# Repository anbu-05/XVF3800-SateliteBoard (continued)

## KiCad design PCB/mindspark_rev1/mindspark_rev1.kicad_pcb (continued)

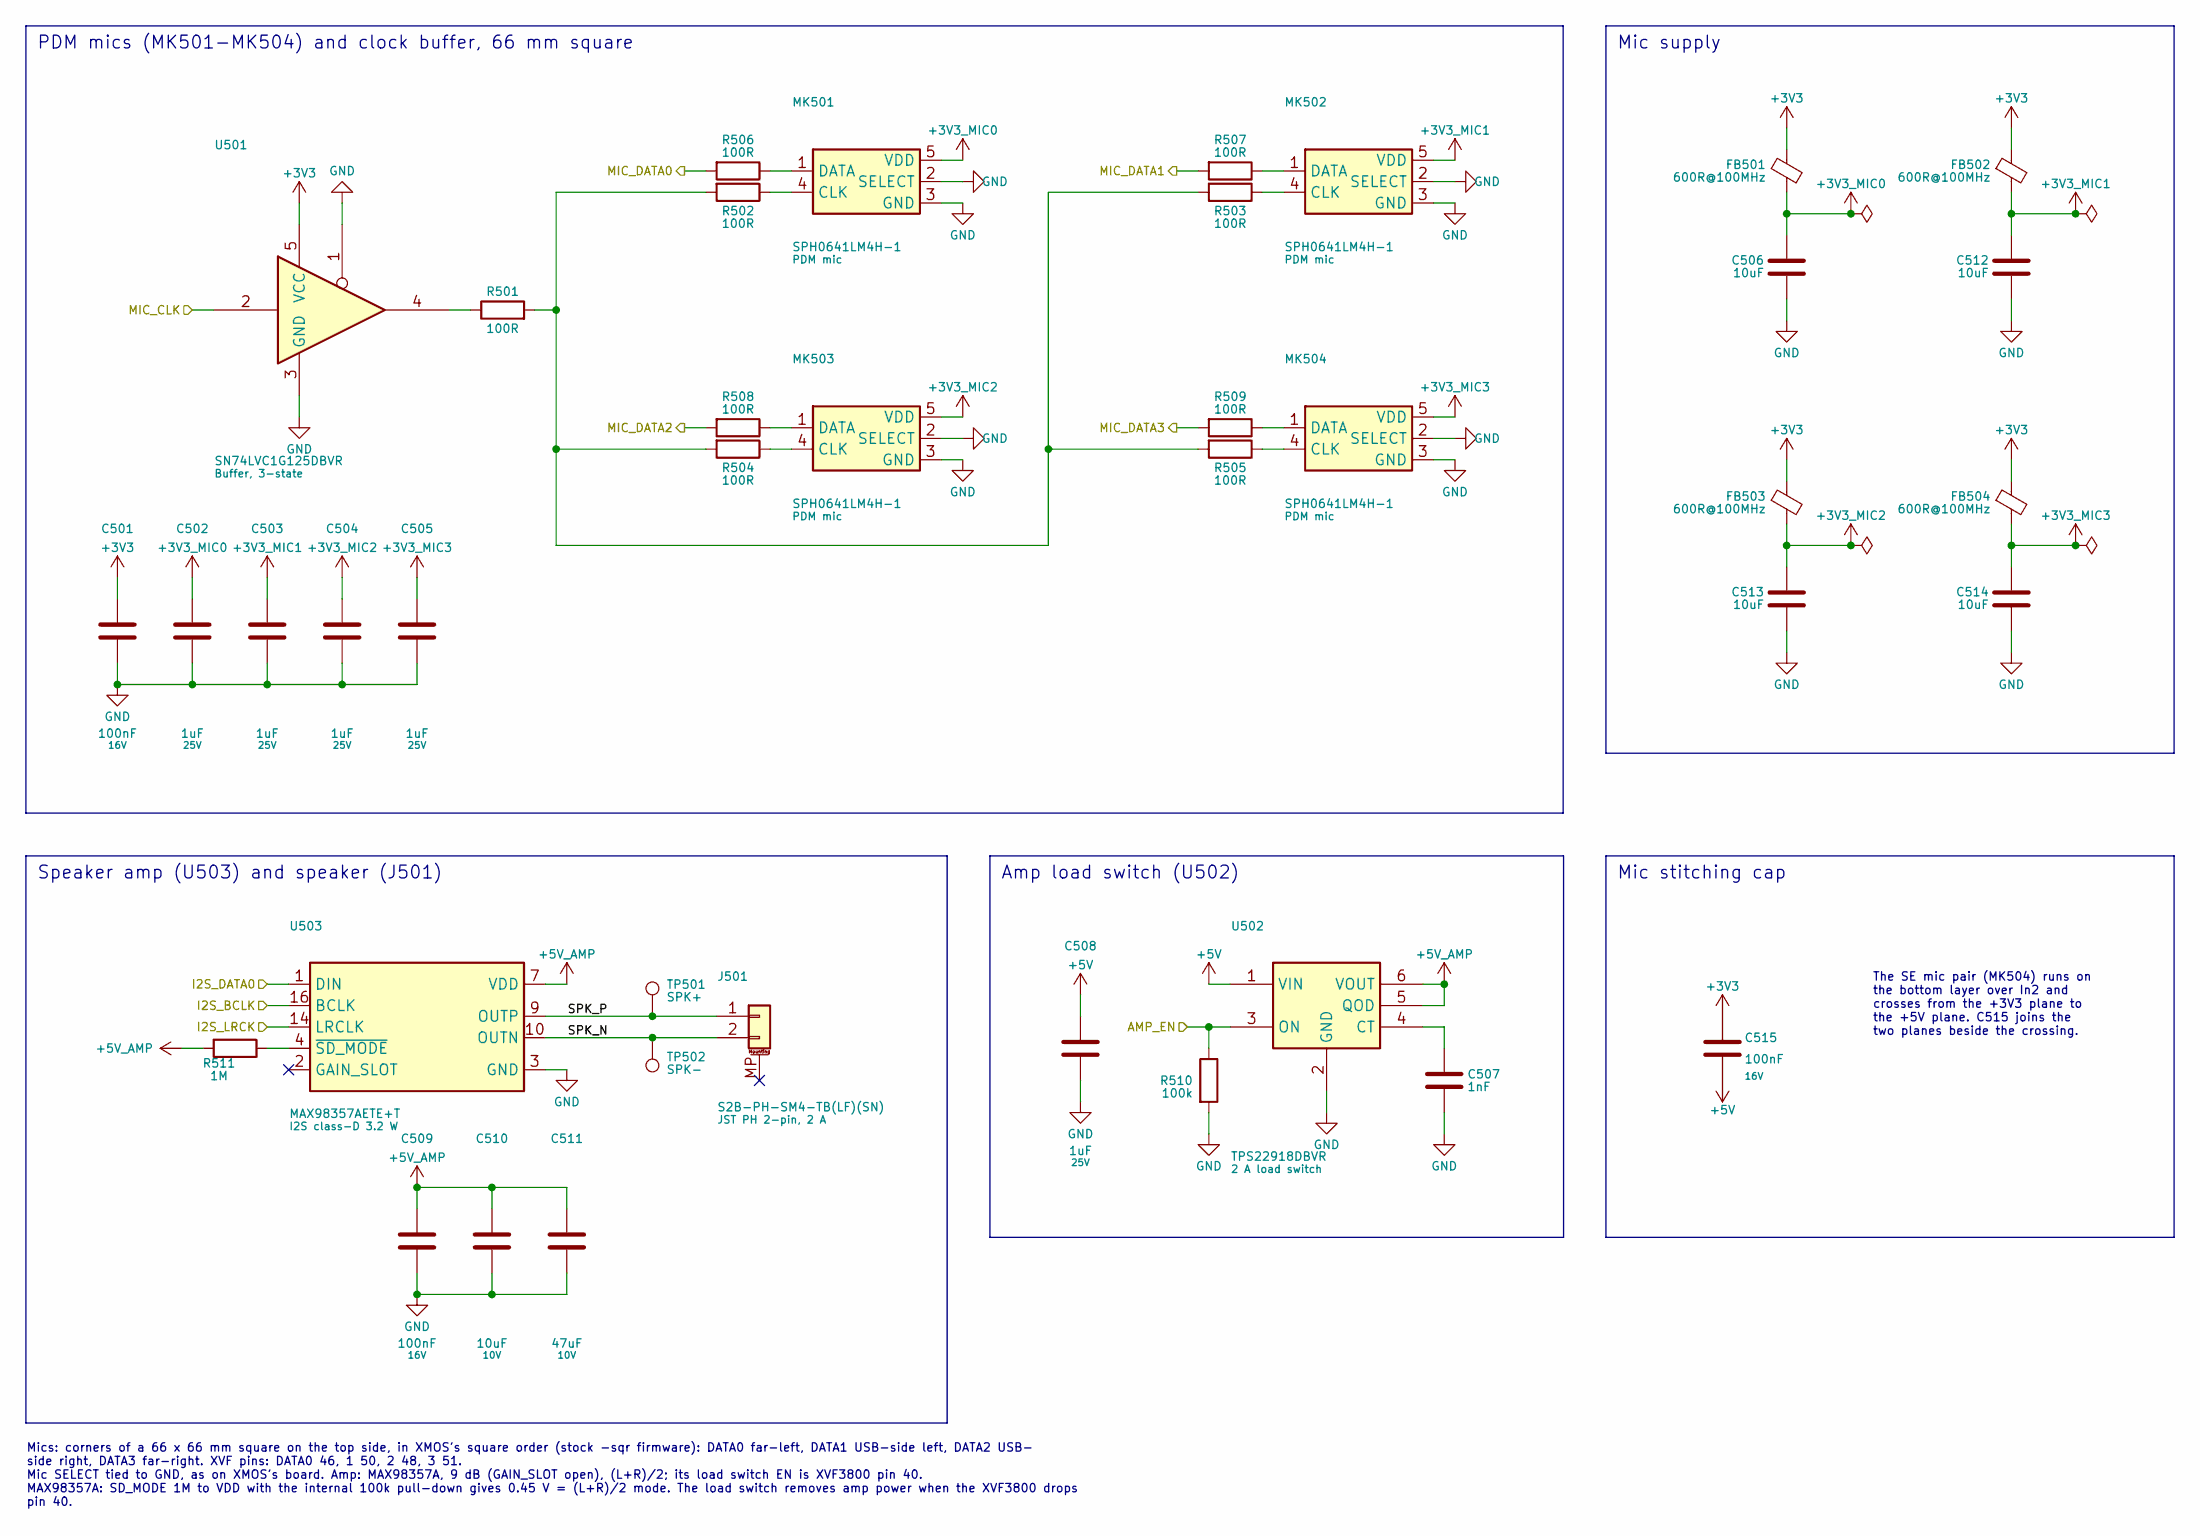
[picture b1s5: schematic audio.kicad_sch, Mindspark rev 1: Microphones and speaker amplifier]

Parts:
C501, C509, C515: 100nF; C_0402_1005Metric; voltage 16V; MPN CL05B104KO5NNNC; LCSC C1525
C502, C503, C504, C505, C508: 1uF; C_0402_1005Metric; voltage 25V; MPN CL05A105KA5NQNC; LCSC C52923
C506, C510, C512, C513, C514: 10uF; C_0603_1608Metric; voltage 10V; MPN CL10A106KP8NNNC; LCSC C19702
C507: 1nF; C_0402_1005Metric; voltage 50V; MPN 0402B102K500NT; LCSC C1523
C511: 47uF; C_1206_3216Metric; voltage 10V; MPN CL31A476MPHNNNE; LCSC C96123
FB501, FB502, FB503, FB504: 600R@100MHz; L_0402_1005Metric; MPN BLM15AG601SN1D; LCSC C76884
J501: S2B-PH-SM4-TB(LF)(SN); JST_PH_S2B-PH-SM4-TB_1x02-1MP_P2.00mm_Horizontal; MPN S2B-PH-SM4-TB(LF)(SN); LCSC C295747
MK501, MK502, MK503, MK504: SPH0641LM4H-1; Knowles_SPH0641LM4H-1_LGA-5_3.5x2.65mm; MPN SPH0641LM4H-1; LCSC C497724
R501, R502, R503, R504, R505, R506, R507, R508, R509: 100R; R_0402_1005Metric; tolerance 1%; MPN 0402WGF1000TCE; LCSC C25076
R510: 100k; R_0402_1005Metric; tolerance 1%; MPN 0402WGF1003TCE; LCSC C25741
R511: 1M; R_0402_1005Metric; tolerance 1%; MPN 0402WGF1004TCE; LCSC C26083
TP501: SPK+; TestPoint_Pad_1.0x1.0mm
TP502: SPK-; TestPoint_Pad_1.0x1.0mm
U501: SN74LVC1G125DBVR; SOT-23-5; MPN SN74LVC1G125DBVR; LCSC C23654
U502: TPS22918DBVR; SOT-23-6; MPN TPS22918DBVR; LCSC C131941
U503: MAX98357AETE+T; TQFN-16-1EP_3x3mm_P0.5mm_EP1.23x1.23mm; MPN MAX98357AETE+T; LCSC C910544

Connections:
+3V3: C501.1, C515.1, FB501.1, FB502.1, FB503.1, FB504.1, U501.5 (VCC); also elsewhere on the board
+3V3_MIC0: C502.1, C506.1, FB501.2, MK501.5 (VDD)
+3V3_MIC1: C503.1, C512.1, FB502.2, MK502.5 (VDD)
+3V3_MIC2: C504.1, C513.1, FB503.2, MK503.5 (VDD)
+3V3_MIC3: C505.1, C514.1, FB504.2, MK504.5 (VDD)
+5V: C508.1, C515.2, U502.1 (VIN); also elsewhere on the board
+5V_AMP: C509.1, C510.1, C511.1, R511.2, U502.5 (QOD), U502.6 (VOUT), U503.7 (VDD), U503.8 (VDD)
/AMP_EN: R510.1, U502.3 (ON); also elsewhere on the board
/I2S_BCLK: U503.16 (BCLK); also elsewhere on the board
/I2S_DATA0: U503.1 (DIN); also elsewhere on the board
/I2S_LRCK: U503.14 (LRCLK); also elsewhere on the board
/MIC_CLK: U501.2; also elsewhere on the board
/MIC_DATA0: R506.2; also elsewhere on the board
/MIC_DATA1: R507.2; also elsewhere on the board
/MIC_DATA2: R508.2; also elsewhere on the board
/MIC_DATA3: R509.2; also elsewhere on the board
/audio/SPK_N: J501.2, TP502.1 (1_1), U503.10 (OUTN)
/audio/SPK_P: J501.1, TP501.1 (1_1), U503.9 (OUTP)
GND: C501.2, C502.2, C503.2, C504.2, C505.2, C506.2, C507.2, C508.2, C509.2, C510.2, C511.2, C512.2, C513.2, C514.2, MK501.2 (SELECT), MK501.3 (GND), MK502.2 (SELECT), MK502.3 (GND), MK503.2 (SELECT), MK503.3 (GND), MK504.2 (SELECT), MK504.3 (GND), R510.2, U501.1, U501.3 (GND), U502.2 (GND), U503.3 (GND), U503.11 (GND), U503.15 (GND), U503.17 (GND); also elsewhere on the board
unnamed: MK501.4 (CLK), R502.1
unnamed: MK501.1 (DATA), R506.1
unnamed: MK502.4 (CLK), R503.1
unnamed: MK502.1 (DATA), R507.1
unnamed: MK503.4 (CLK), R504.1
unnamed: MK503.1 (DATA), R508.1
unnamed: MK504.4 (CLK), R505.1
unnamed: MK504.1 (DATA), R509.1
unnamed: R501.1, U501.4
unnamed: R501.2, R502.2, R503.2, R504.2, R505.2
unnamed: C507.1, U502.4 (CT)
unnamed: R511.1, U503.4 (~SD_MODE)

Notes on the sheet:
Mics: corners of a 66 x 66 mm square on the top side, in XMOS's square order (stock -sqr firmware): DATA0 far-left, DATA1 USB-side left, DATA2 USB- side right, DATA3 far-right. XVF pins: DATA0 46, 1 50, 2 48, 3 51. Mic SELECT tied to GND, as on XMOS's board. Amp: MAX98357A, 9 dB (GAIN_SLOT open), (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
PDM mics (MK501-MK504) and clock buffer, 66 mm square
Mic supply
Speaker amp (U503) and speaker (J501)
Amp load switch (U502)
Mic stitching cap
The SE mic pair (MK504) runs on the bottom layer over In2 and crosses from the +3V3 plane to the +5V plane. C515 joins the two planes beside the crossing.

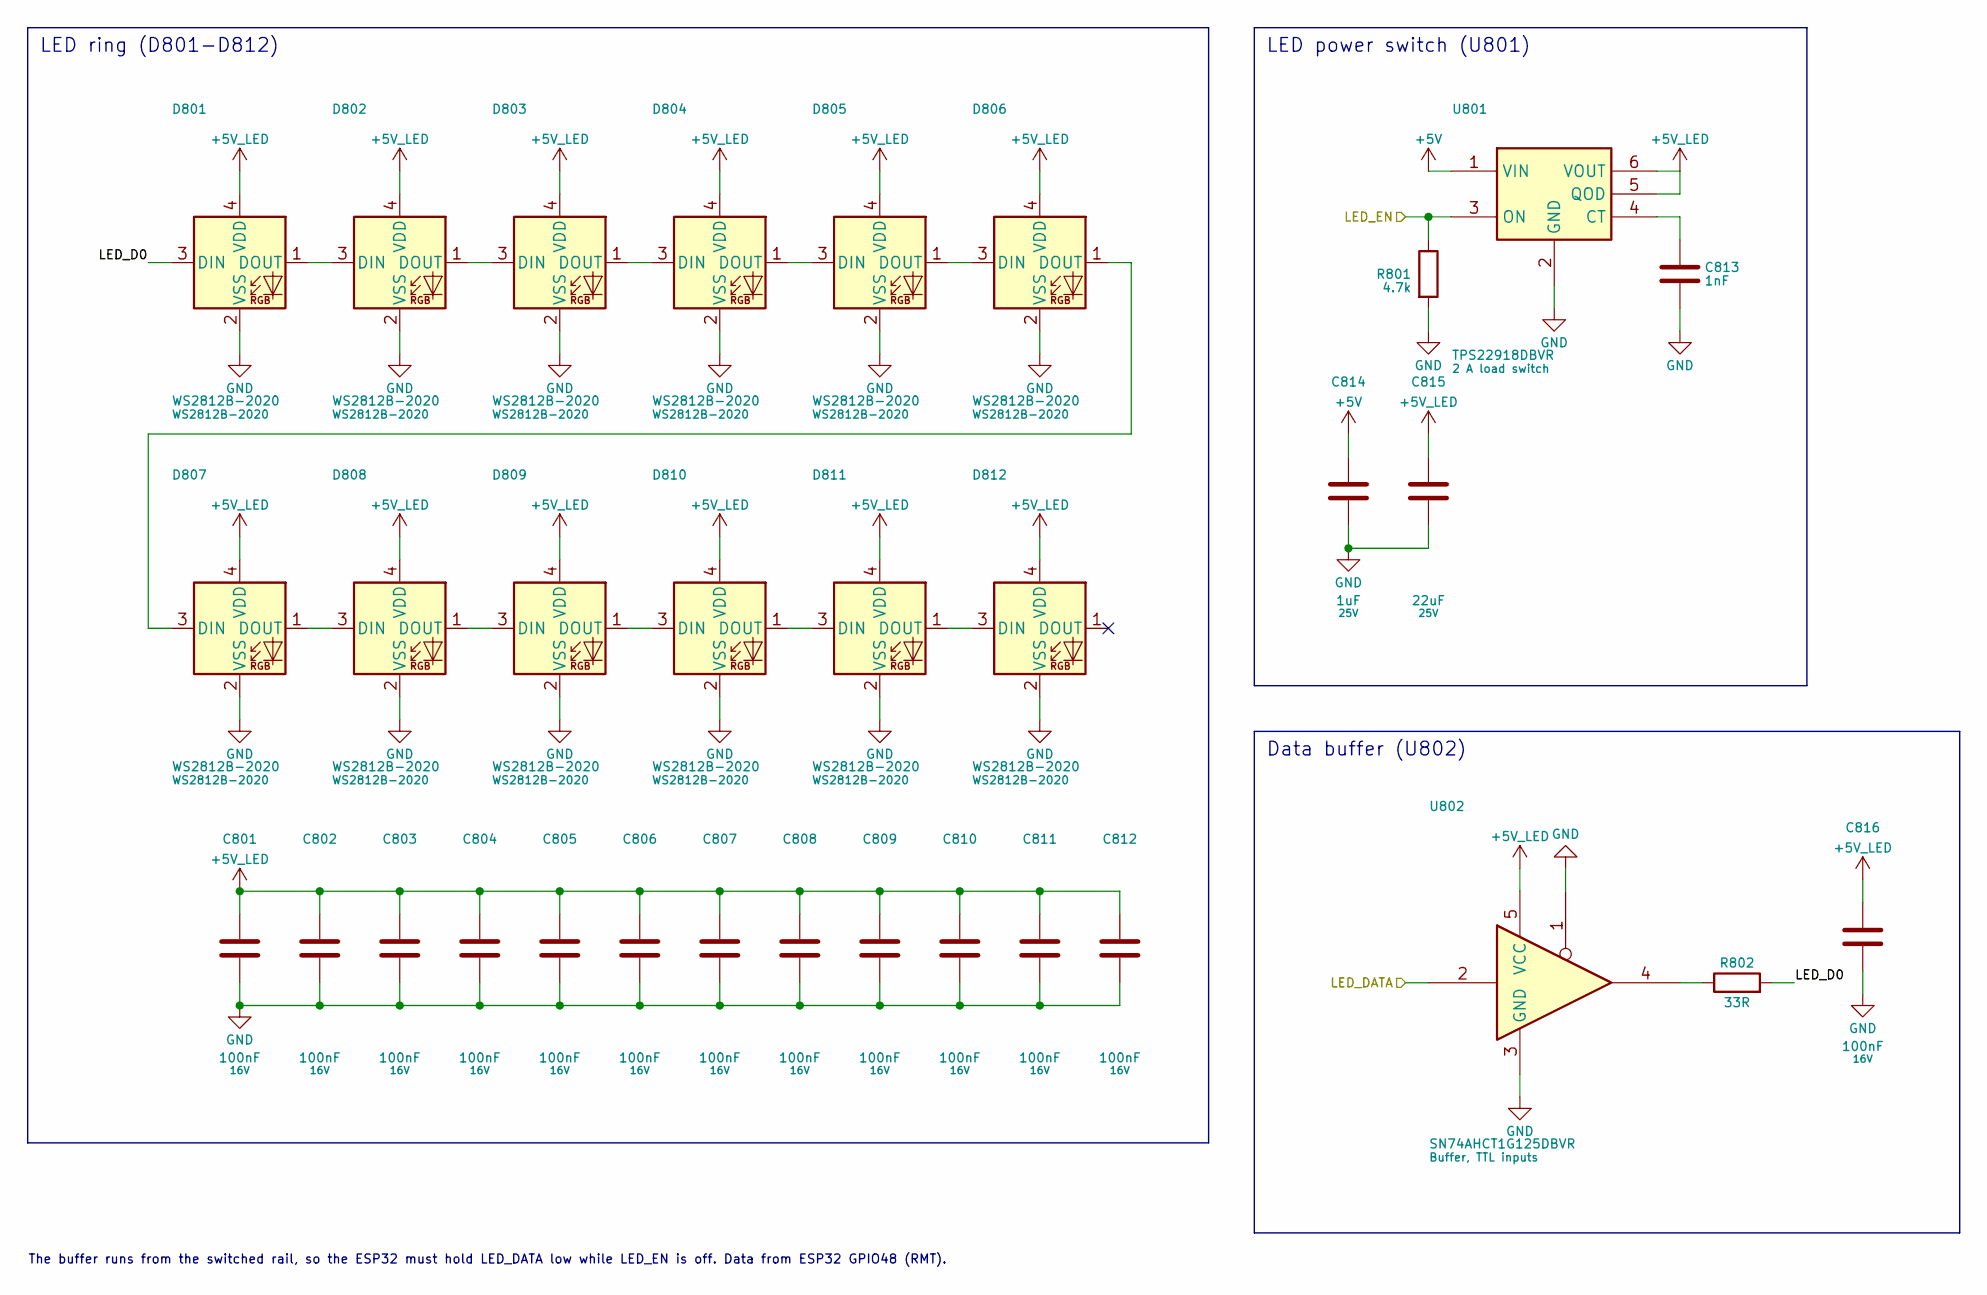
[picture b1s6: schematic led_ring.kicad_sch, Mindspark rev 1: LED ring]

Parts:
C801, C802, C803, C804, C805, C806, C807, C808, C809, C810, C811, C812, C816: 100nF; C_0402_1005Metric; voltage 16V; MPN CL05B104KO5NNNC; LCSC C1525
C813: 1nF; C_0402_1005Metric; voltage 50V; MPN 0402B102K500NT; LCSC C1523
C814: 1uF; C_0402_1005Metric; voltage 25V; MPN CL05A105KA5NQNC; LCSC C52923
C815: 22uF; C_0805_2012Metric; voltage 25V; MPN CL21A226MAQNNNE; LCSC C45783
D801, D802, D803, D804, D805, D806, D807, D808, D809, D810, D811, D812: WS2812B-2020; LED_WS2812B-2020_PLCC4_2.0x2.0mm; MPN WS2812B-2020-V6; LCSC C52917434
R801: 4.7k; R_0402_1005Metric; tolerance 1%; MPN 0402WGF4701TCE; LCSC C25900
R802: 33R; R_0402_1005Metric; tolerance 1%; MPN 0402WGF330JTCE; LCSC C25105
U801: TPS22918DBVR; SOT-23-6; MPN TPS22918DBVR; LCSC C131941
U802: SN74AHCT1G125DBVR; SOT-23-5; MPN SN74AHCT1G125DBVR; LCSC C7484

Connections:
+5V: C814.1, U801.1 (VIN); also elsewhere on the board
+5V_LED: C801.1, C802.1, C803.1, C804.1, C805.1, C806.1, C807.1, C808.1, C809.1, C810.1, C811.1, C812.1, C815.1, C816.1, D801.4 (VDD), D802.4 (VDD), D803.4 (VDD), D804.4 (VDD), D805.4 (VDD), D806.4 (VDD), D807.4 (VDD), D808.4 (VDD), D809.4 (VDD), D810.4 (VDD), D811.4 (VDD), D812.4 (VDD), U801.5 (QOD), U801.6 (VOUT), U802.5 (VCC)
/LED_DATA: U802.2; also elsewhere on the board
/LED_EN: R801.1, U801.3 (ON); also elsewhere on the board
/led_ring/LED_D0: D801.3 (DIN), R802.2
GND: C801.2, C802.2, C803.2, C804.2, C805.2, C806.2, C807.2, C808.2, C809.2, C810.2, C811.2, C812.2, C813.2, C814.2, C815.2, C816.2, D801.2 (VSS), D802.2 (VSS), D803.2 (VSS), D804.2 (VSS), D805.2 (VSS), D806.2 (VSS), D807.2 (VSS), D808.2 (VSS), D809.2 (VSS), D810.2 (VSS), D811.2 (VSS), D812.2 (VSS), R801.2, U801.2 (GND), U802.1, U802.3 (GND); also elsewhere on the board
unnamed: D801.1 (DOUT), D802.3 (DIN)
unnamed: D802.1 (DOUT), D803.3 (DIN)
unnamed: D803.1 (DOUT), D804.3 (DIN)
unnamed: D804.1 (DOUT), D805.3 (DIN)
unnamed: D805.1 (DOUT), D806.3 (DIN)
unnamed: D806.1 (DOUT), D807.3 (DIN)
unnamed: D807.1 (DOUT), D808.3 (DIN)
unnamed: D808.1 (DOUT), D809.3 (DIN)
unnamed: D809.1 (DOUT), D810.3 (DIN)
unnamed: D810.1 (DOUT), D811.3 (DIN)
unnamed: D811.1 (DOUT), D812.3 (DIN)
unnamed: R802.1, U802.4
unnamed: C813.1, U801.4 (CT)

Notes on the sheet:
The buffer runs from the switched rail, so the ESP32 must hold LED_DATA low while LED_EN is off. Data from ESP32 GPIO48 (RMT).
LED power switch (U801)
Data buffer (U802)
LED ring (D801-D812)

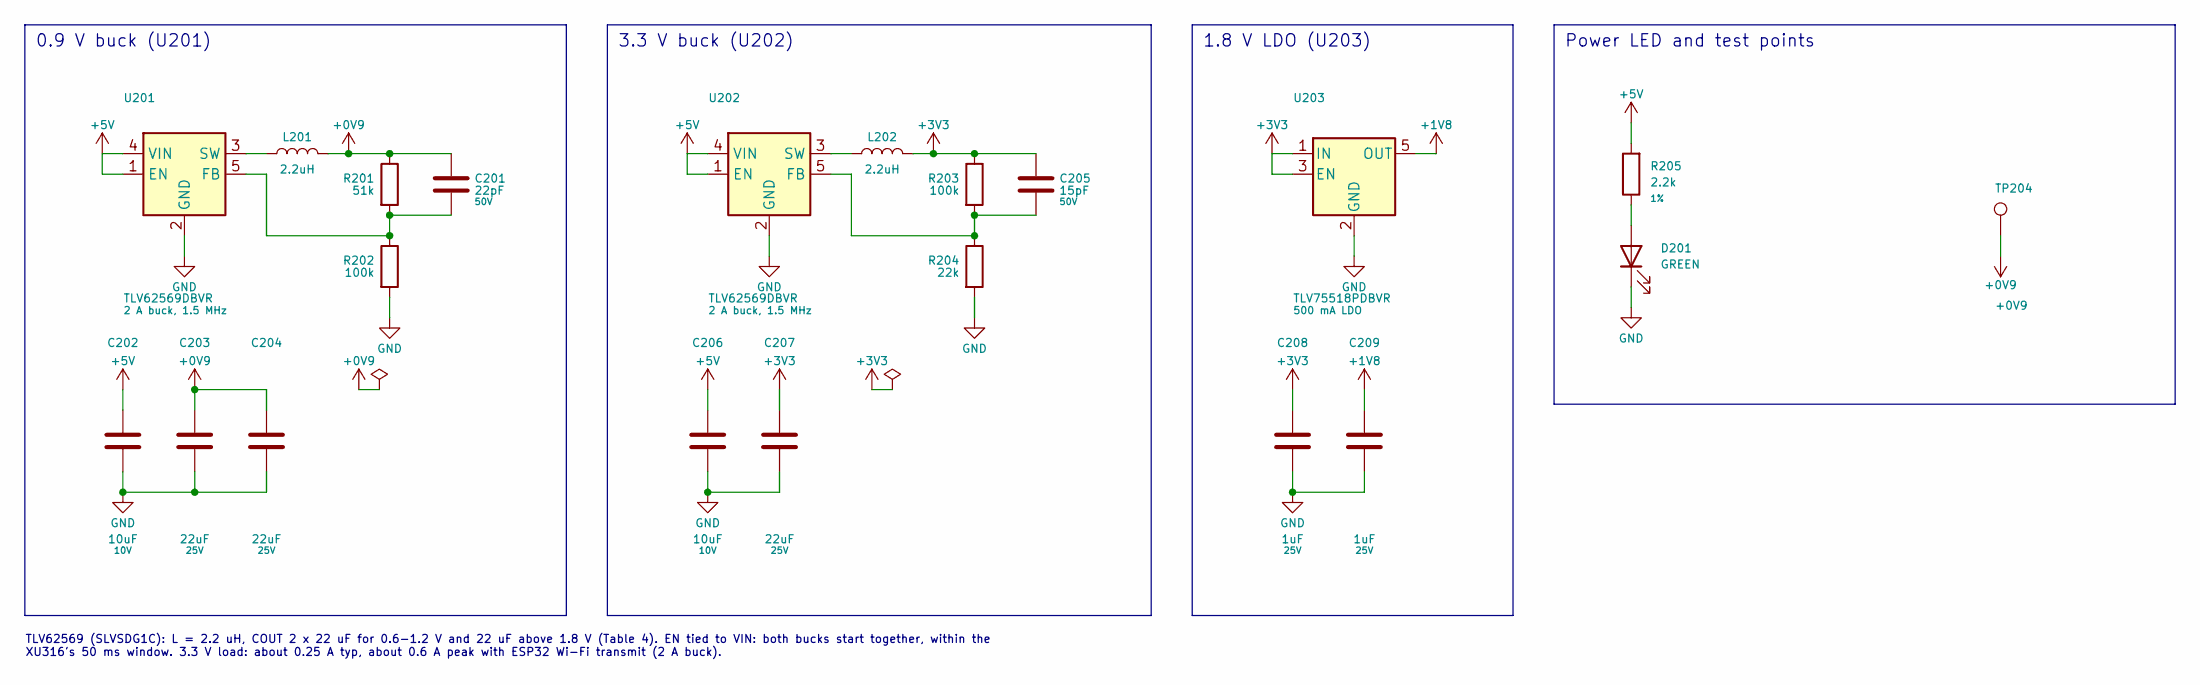
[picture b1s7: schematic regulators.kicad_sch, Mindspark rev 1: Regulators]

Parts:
C201: 22pF; C_0402_1005Metric; voltage 50V; MPN 0402CG220J500NT; LCSC C1555
C202, C206: 10uF; C_0603_1608Metric; voltage 10V; MPN CL10A106KP8NNNC; LCSC C19702
C203, C204, C207: 22uF; C_0805_2012Metric; voltage 25V; MPN CL21A226MAQNNNE; LCSC C45783
C205: 15pF; C_0402_1005Metric; voltage 50V; MPN 0402CG150J500NT; LCSC C1548
C208, C209: 1uF; C_0402_1005Metric; voltage 25V; MPN CL05A105KA5NQNC; LCSC C52923
D201: GREEN; LED_0603_1608Metric; MPN KT-0603G; LCSC C12624
L201, L202: 2.2uH; L_Bourns_SRP4020TA; MPN SRP4020TA-2R2M; LCSC C719179
R201: 51k; R_0402_1005Metric; tolerance 1%; MPN 0402WGF5102TCE; LCSC C25794
R202, R203: 100k; R_0402_1005Metric; tolerance 1%; MPN 0402WGF1003TCE; LCSC C25741
R204: 22k; R_0402_1005Metric; tolerance 1%; MPN 0402WGF2202TCE; LCSC C25768
R205: 2.2k; R_0402_1005Metric; tolerance 1%; MPN 0402WGF2201TCE; LCSC C25879
TP204: +0V9; TestPoint_Pad_D1.0mm
U201, U202: TLV62569DBVR; SOT-23-5; MPN TLV62569DBVR; LCSC C141836
U203: TLV75518PDBVR; SOT-23-5; MPN TLV75518PDBVR; LCSC C2877863

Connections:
+0V9: C201.1, C203.1, C204.1, L201.2, R201.1, TP204.1 (1_1); also elsewhere on the board
+1V8: C209.1, U203.5 (OUT); also elsewhere on the board
+3V3: C205.1, C207.1, C208.1, L202.2, R203.1, U203.1 (IN), U203.3 (EN); also elsewhere on the board
+5V: C202.1, C206.1, R205.2, U201.1 (EN), U201.4 (VIN), U202.1 (EN), U202.4 (VIN); also elsewhere on the board
GND: C202.2, C203.2, C204.2, C206.2, C207.2, C208.2, C209.2, D201.1 (K), R202.2, R204.2, U201.2 (GND), U202.2 (GND), U203.2 (GND); also elsewhere on the board
unnamed: D201.2 (A), R205.1
unnamed: C201.2, R201.2, R202.1, U201.5 (FB)
unnamed: L201.1, U201.3 (SW)
unnamed: C205.2, R203.2, R204.1, U202.5 (FB)
unnamed: L202.1, U202.3 (SW)

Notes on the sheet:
0.9 V buck (U201)
Power LED and test points
1.8 V LDO (U203)
3.3 V buck (U202)
TLV62569 (SLVSDG1C): L = 2.2 uH, COUT 2 x 22 uF for 0.6-1.2 V and 22 uF above 1.8 V (Table 4). EN tied to VIN: both bucks start together, within the XU316's 50 ms window. 3.3 V load: about 0.25 A typ, about 0.6 A peak with ESP32 Wi-Fi transmit (2 A buck).

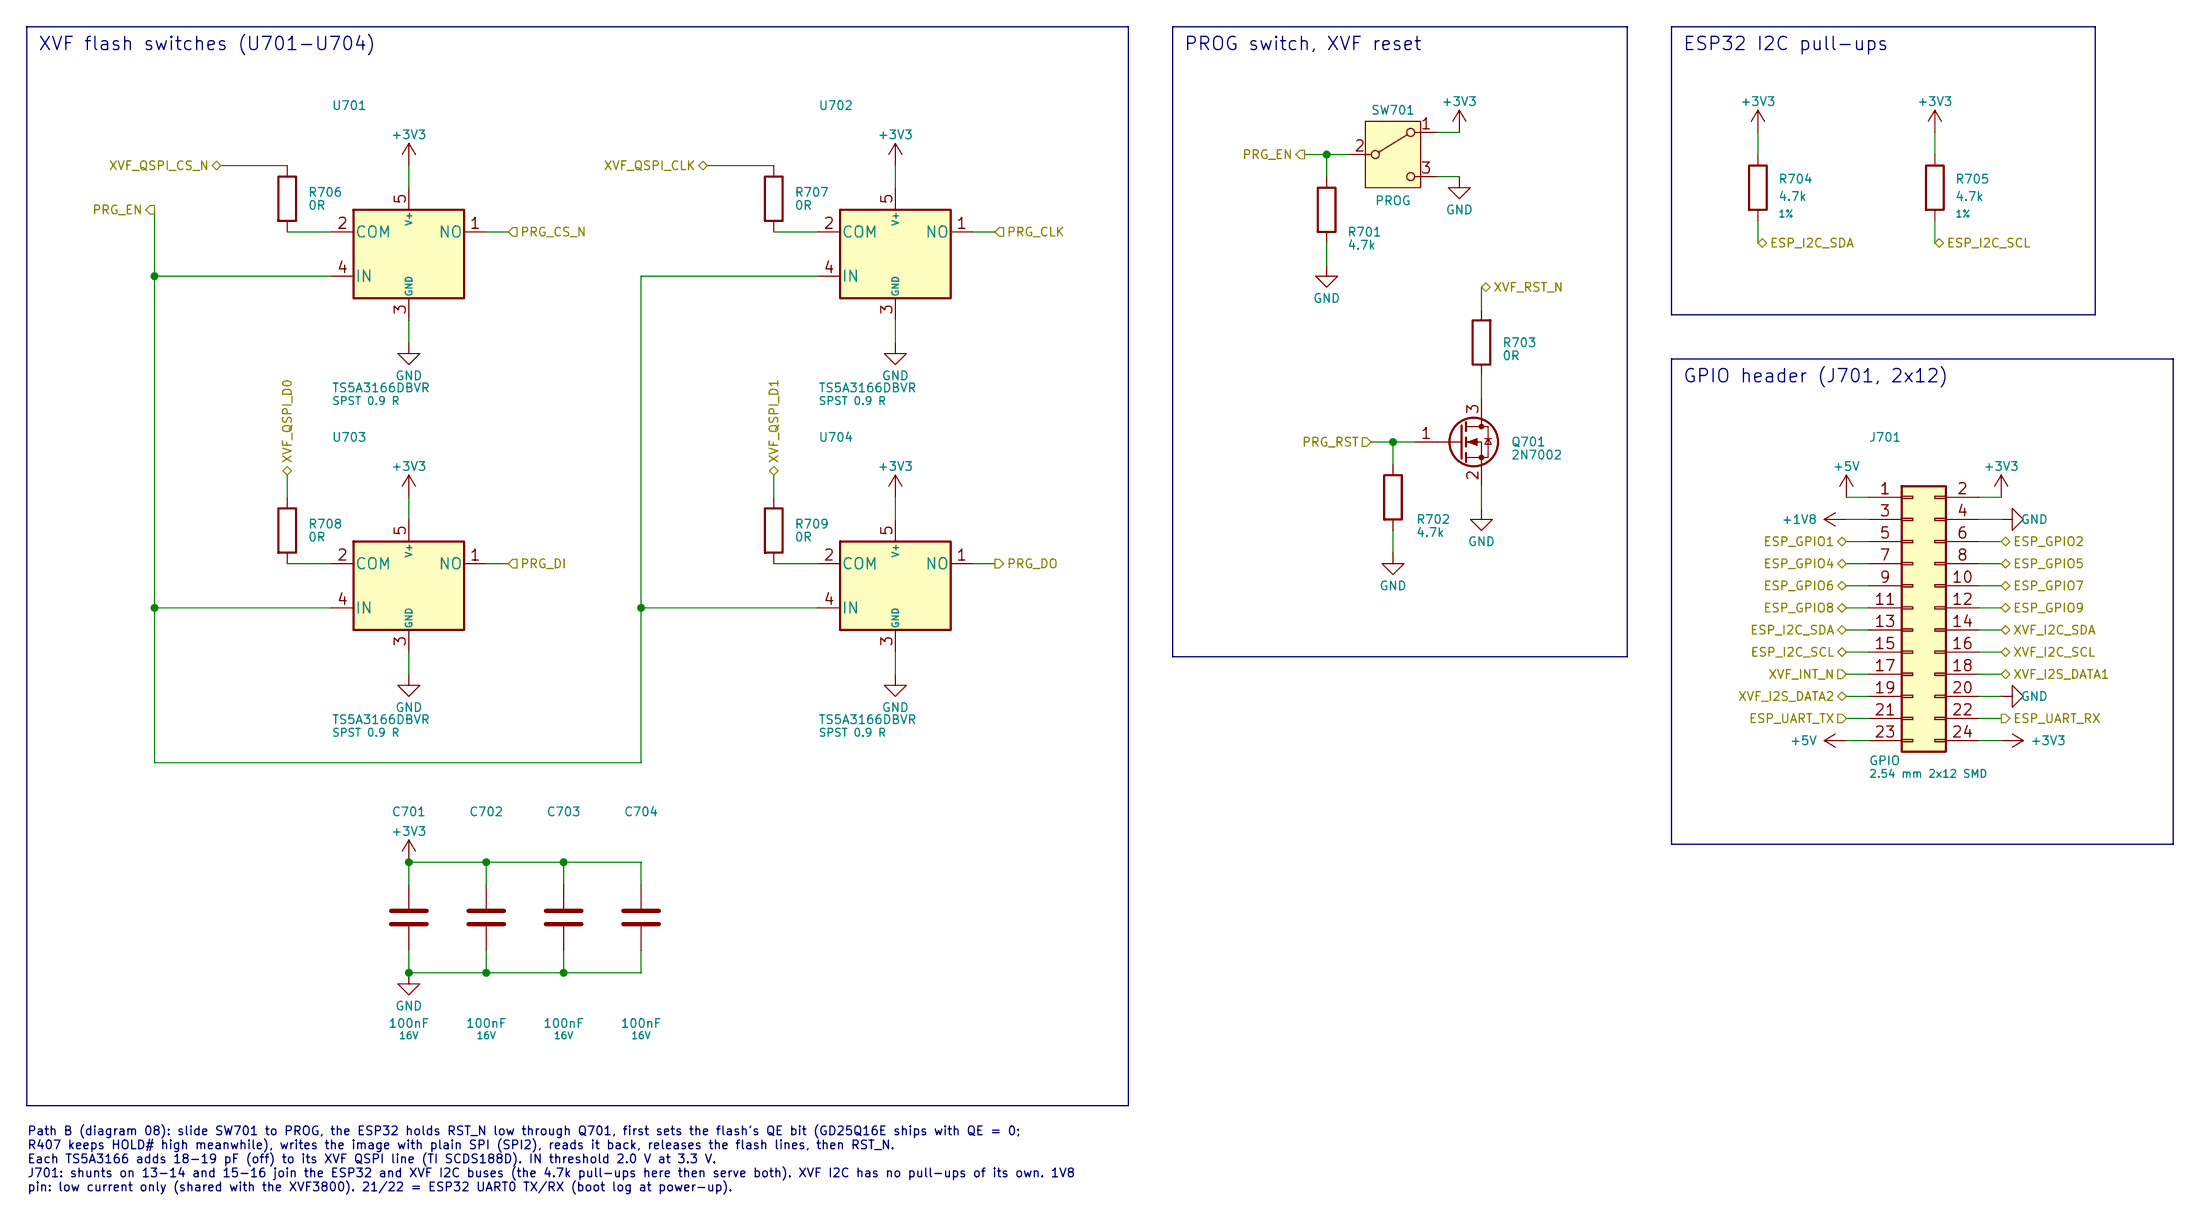
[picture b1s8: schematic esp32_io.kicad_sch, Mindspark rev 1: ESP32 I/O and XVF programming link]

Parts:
C701, C702, C703, C704: 100nF; C_0402_1005Metric; voltage 16V; MPN CL05B104KO5NNNC; LCSC C1525
J701: GPIO; PinHeader_2x12_P2.54mm_Vertical_SMD_HCTL_PZ254; MPN PZ254-2-12-S; LCSC C3294470
Q701: 2N7002; SOT-23; MPN 2N7002; LCSC C8545
R701, R702, R704, R705: 4.7k; R_0402_1005Metric; tolerance 1%; MPN 0402WGF4701TCE; LCSC C25900
R703, R706, R707, R708, R709: 0R; R_0402_1005Metric; tolerance 1%; MPN 0402WGF0000TCE; LCSC C17168
SW701: PROG; SW_SHOUHAN_MSK12C02_SideActuated; MPN MSK12C02; LCSC C431540
U701, U702, U703, U704: TS5A3166DBVR; SOT-23-5; MPN TS5A3166DBVR; LCSC C353035

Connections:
+1V8: J701.3; also elsewhere on the board
+3V3: C701.1, C702.1, C703.1, C704.1, J701.2, J701.24, R704.1, R705.1, SW701.1 (A), U701.5 (V+), U702.5 (V+), U703.5 (V+), U704.5 (V+); also elsewhere on the board
+5V: J701.1, J701.23; also elsewhere on the board
/ESP_GPIO1: J701.5; also elsewhere on the board
/ESP_GPIO2: J701.6; also elsewhere on the board
/ESP_GPIO4: J701.7; also elsewhere on the board
/ESP_GPIO5: J701.8; also elsewhere on the board
/ESP_GPIO6: J701.9; also elsewhere on the board
/ESP_GPIO7: J701.10; also elsewhere on the board
/ESP_GPIO8: J701.11; also elsewhere on the board
/ESP_GPIO9: J701.12; also elsewhere on the board
/ESP_I2C_SCL: J701.15, R705.2; also elsewhere on the board
/ESP_I2C_SDA: J701.13, R704.2; also elsewhere on the board
/ESP_UART_RX: J701.22; also elsewhere on the board
/ESP_UART_TX: J701.21; also elsewhere on the board
/PRG_CLK: U702.1 (NO); also elsewhere on the board
/PRG_CS_N: U701.1 (NO); also elsewhere on the board
/PRG_DI: U703.1 (NO); also elsewhere on the board
/PRG_DO: U704.1 (NO); also elsewhere on the board
/PRG_EN: R701.1, SW701.2 (B), U701.4 (IN), U702.4 (IN), U703.4 (IN), U704.4 (IN); also elsewhere on the board
/PRG_RST: Q701.1 (G), R702.1; also elsewhere on the board
/XVF_I2C_SCL: J701.16; also elsewhere on the board
/XVF_I2C_SDA: J701.14; also elsewhere on the board
/XVF_I2S_DATA1: J701.18; also elsewhere on the board
/XVF_I2S_DATA2: J701.19; also elsewhere on the board
/XVF_INT_N: J701.17; also elsewhere on the board
/XVF_QSPI_CLK: R707.1; also elsewhere on the board
/XVF_QSPI_CS_N: R706.1; also elsewhere on the board
/XVF_QSPI_D0: R708.1; also elsewhere on the board
/XVF_QSPI_D1: R709.1; also elsewhere on the board
/XVF_RST_N: R703.2; also elsewhere on the board
GND: C701.2, C702.2, C703.2, C704.2, J701.4, J701.20, Q701.2 (S), R701.2, R702.2, SW701.3 (C), U701.3 (GND), U702.3 (GND), U703.3 (GND), U704.3 (GND); also elsewhere on the board
unnamed: Q701.3 (D), R703.1
unnamed: R706.2, U701.2 (COM)
unnamed: R707.2, U702.2 (COM)
unnamed: R708.2, U703.2 (COM)
unnamed: R709.2, U704.2 (COM)

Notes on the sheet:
XVF flash switches (U701-U704)
ESP32 I2C pull-ups
PROG switch, XVF reset
GPIO header (J701, 2x12)
Path B (diagram 08): slide SW701 to PROG, the ESP32 holds RST_N low through Q701, first sets the flash's QE bit (GD25Q16E ships with QE = 0; R407 keeps HOLD# high meanwhile), writes the image with plain SPI (SPI2), reads it back, releases the flash lines, then RST_N. Each TS5A3166 adds 18-19 pF (of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

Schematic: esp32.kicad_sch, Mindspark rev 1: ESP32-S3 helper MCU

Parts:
C601: 22uF; C_0805_2012Metric; voltage 25V; MPN CL21A226MAQNNNE; LCSC C45783
C602, C604, C605: 100nF; C_0402_1005Metric; voltage 16V; MPN CL05B104KO5NNNC; LCSC C1525
C603: 1uF; C_0402_1005Metric; voltage 25V; MPN CL05A105KA5NQNC; LCSC C52923
D601: WS2812B-2020; LED_WS2812B-2020_PLCC4_2.0x2.0mm; MPN WS2812B-2020-V6; LCSC C52917434
R601, R602, R607: 10k; R_0402_1005Metric; tolerance 1%; MPN 0402WGF1002TCE; LCSC C25744
R603, R604, R609: 1k; R_0402_1005Metric; tolerance 1%; MPN 0402WGF1001TCE; LCSC C11702
R605, R606: 27R; R_0402_1005Metric; tolerance 1%; MPN 0402WGF270JTCE; LCSC C25100
R608: 33R; R_0402_1005Metric; tolerance 1%; MPN 0402WGF330JTCE; LCSC C25105
SW601: EN; SW_Push_1P1T_XKB_TS-1187A; MPN TS-1187A-B-A-B; LCSC C318884
SW602: BOOT; SW_Push_1P1T_XKB_TS-1187A; MPN TS-1187A-B-A-B; LCSC C318884
SW603: USER; SW_SHOUHAN_TS24CA_SideActuated; MPN TS24CA; LCSC C393942
U601: ESP32-S3-WROOM-1U-N16R8; ESP32-S3-WROOM-1U; MPN ESP32-S3-WROOM-1U-N16R8; LCSC C3013946
U602: SN74AHCT1G125DBVR; SOT-23-5; MPN SN74AHCT1G125DBVR; LCSC C7484

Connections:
+3V3: C601.1, C602.1, R601.2, R602.2, R607.1, U601.2 (3V3); also elsewhere on the board
+5V: C604.1, C605.1, D601.4 (VDD), U602.5 (VCC); also elsewhere on the board
/ESP_GPIO1: U601.39 (IO1); also elsewhere on the board
/ESP_GPIO2: U601.38 (IO2); also elsewhere on the board
/ESP_GPIO4: U601.4 (IO4); also elsewhere on the board
/ESP_GPIO5: U601.5 (IO5); also elsewhere on the board
/ESP_GPIO6: U601.6 (IO6); also elsewhere on the board
/ESP_GPIO7: U601.7 (IO7); also elsewhere on the board
/ESP_GPIO8: U601.12 (IO8); also elsewhere on the board
/ESP_GPIO9: U601.17 (IO9); also elsewhere on the board
/ESP_I2C_SCL: U601.32 (IO39); also elsewhere on the board
/ESP_I2C_SDA: U601.31 (IO38); also elsewhere on the board
/ESP_MUTE_LED: U601.34 (IO41); also elsewhere on the board
/ESP_UART_RX: U601.36 (RXD0); also elsewhere on the board
/ESP_UART_TX: U601.37 (TXD0); also elsewhere on the board
/LED_DATA: U601.25 (IO48); also elsewhere on the board
/LED_EN: U601.24 (IO47); also elsewhere on the board
/MUX_ST: U601.11 (IO18); also elsewhere on the board
/PRG_CLK: U601.19 (IO11); also elsewhere on the board
/PRG_CS_N: U601.21 (IO13); also elsewhere on the board
/PRG_DI: U601.18 (IO10); also elsewhere on the board
/PRG_DO: U601.20 (IO12); also elsewhere on the board
/PRG_EN: U601.22 (IO14); also elsewhere on the board
/PRG_RST: U601.23 (IO21); also elsewhere on the board
/USB_ESP_DM: R606.2; also elsewhere on the board
/USB_ESP_DP: R605.2; also elsewhere on the board
/XVF_GPO_G: U601.9 (IO16); also elsewhere on the board
/XVF_GPO_R: U601.8 (IO15); also elsewhere on the board
/XVF_INT_N: U601.10 (IO17); also elsewhere on the board
/esp32/BTN_USER_N: R607.2, SW603.1, U601.35 (IO42)
/esp32/ESP_BOOT: R602.1, SW602.1, U601.27 (IO0)
/esp32/ESP_EN: C603.1, R601.1, SW601.1, U601.3 (EN)
/esp32/ESP_USB_DM: R606.1, U601.13 (USB_D-)
/esp32/ESP_USB_DP: R605.1, U601.14 (USB_D+)
/esp32/USER_LED_DATA: U601.33 (IO40), U602.2
GND: C601.2, C602.2, C603.2, C604.2, C605.2, D601.2 (VSS), R603.2, R604.2, R609.2, U601.1 (GND), U601.40 (GND), U601.41 (GND), U602.1, U602.3 (GND); also elsewhere on the board
unnamed: D601.3 (DIN), R608.2
unnamed: R603.1, SW601.2
unnamed: R604.1, SW602.2
unnamed: R608.1, U602.4
unnamed: R609.1, SW603.2

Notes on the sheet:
GPIO: 0 BOOT, 1/2/4-9 2x12 header, 10-13 SPI2 (GPIO matrix) to the XVF flash (10 MOSI=DI, 11 CLK, 12 MISO=DO, 13 CS), 14 PROG switch sense, 15/16 XVF LED_R/G taps, 17 XVF INT_N, 18 mux ST, 19/20 USB, 21 XVF reset (Q701), 38/39 I2C SDA/SCL, 40 user LED, 41 mute LED, 42 user button, 43/44 UART0 TX/RX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
USB series resistors
User button
User RGB LED (D601), own 5 V buffer
ESP32-S3-WROOM-1U-N16R8 (U601)
Supply, EN and BOOT
